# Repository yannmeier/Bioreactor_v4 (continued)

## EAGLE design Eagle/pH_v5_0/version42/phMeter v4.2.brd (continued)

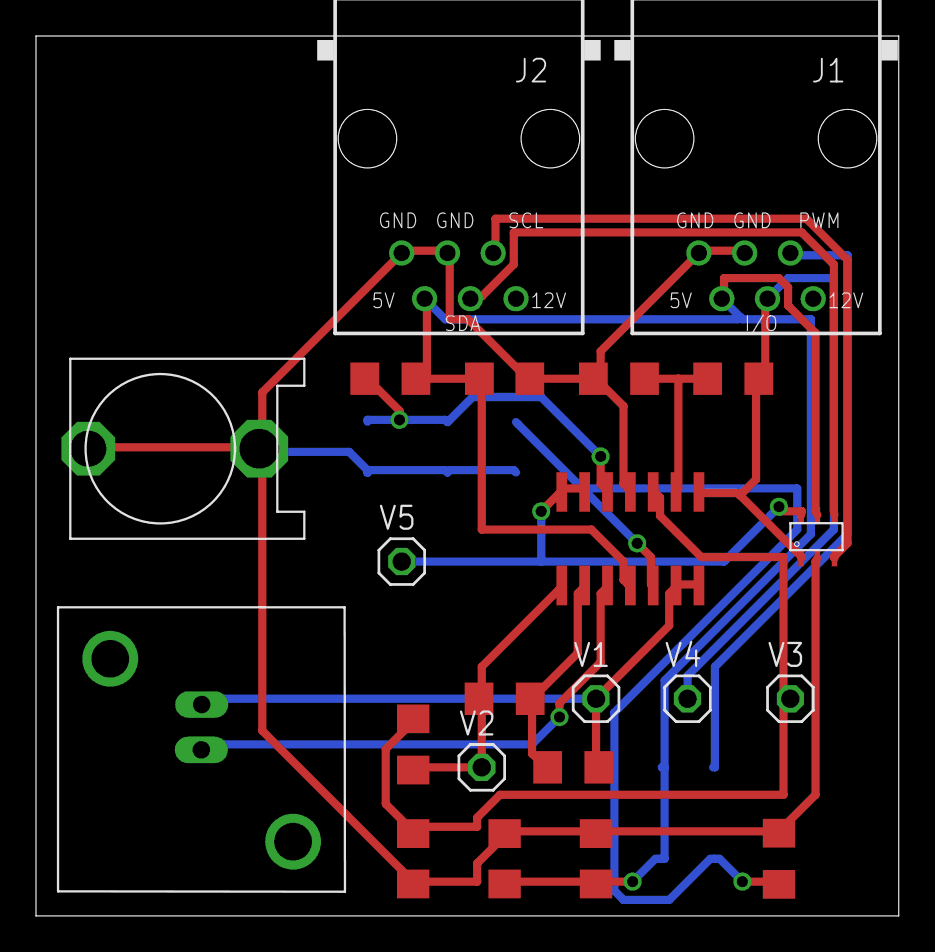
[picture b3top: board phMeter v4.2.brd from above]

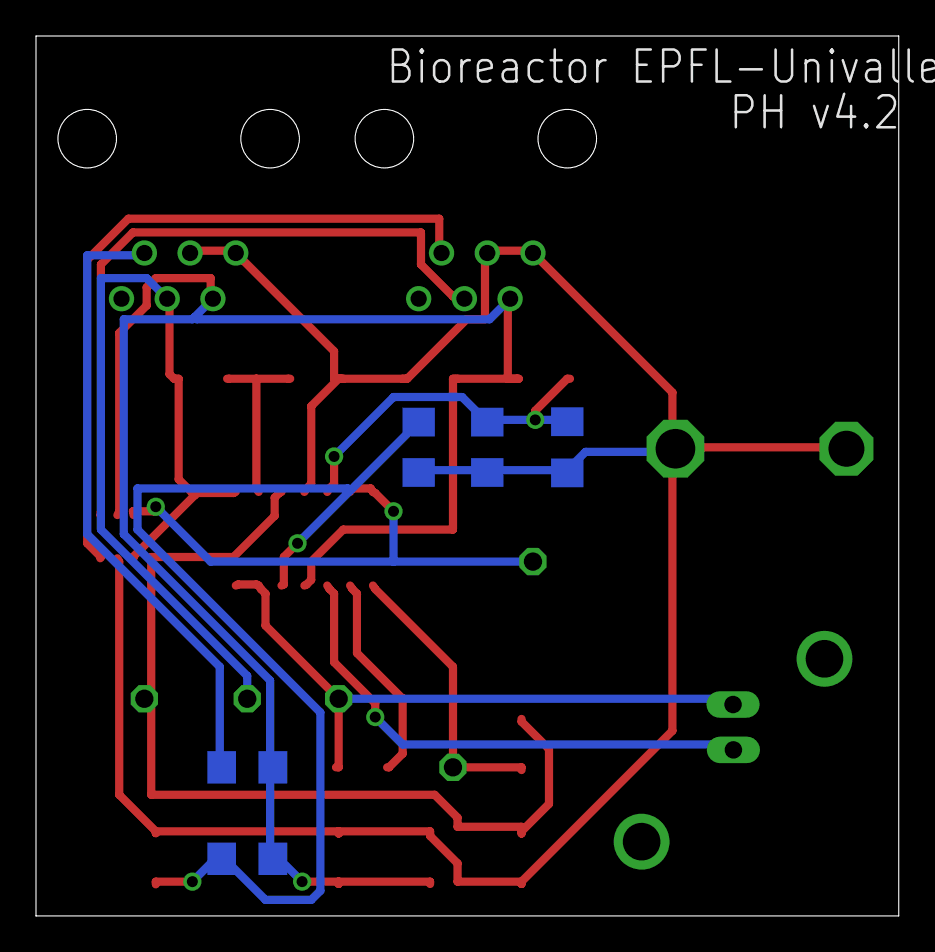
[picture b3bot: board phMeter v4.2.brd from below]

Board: 2 copper layers, 47.9 x 48.9 mm, 27 parts (5 on the bottom side), 15 nets.

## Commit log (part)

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2016-04-12 SPI slave receiving packets, started to implement parsing
2016-04-13 swapped flex connector on LCD SPI, changed D11 pin by the SS/RXLED pin instead, removed SPI pull-up + diode
2016-04-13 send last parameters instead of last logs to the SPI slave LCD
2016-04-13 code cleaning
2016-04-13 Added files via upload
2016-04-13 Created git file in repository
    First Case Prototype
2016-04-13 changed read/write rights n CAD folder
2016-05-07 Fix problem to set parameters with single letter
2016-05-19 bioreactor v4.2 revision, Lora Reset pin on D5, operation at 8MHz, 3.3V. The Flex cable is now exporting 12V instead of 5V (careful, not compatible with LCD V0.2 sudo git add --all), I2C ports are on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
2016-05-24 panelized LCD board v1_0
2016-06-03 corrected bioreactor board for microcircuitos (0.25mm clearance)
2016-07-20 modifications Eric
2016-07-27 CAD files sorted into version folders
2016-07-28 Started working on SPI communication, LCD to master.
2016-08-02 first working SPI communication: transfers one setting at a time. Working on a menu system for the LCD and setting parameters.
2016-08-12 last commit for Eric and Emilien, summer 2016
2016-08-12 Added Documentation and CAD files.
2016-08-16 unziped libraries
2016-10-10 added ref to arduino ide realeases
2016-10-10 debugged version, need to correct onewire to support ds1820, to test the logger(bug here) and lora threads (not compiling)
2016-10-11 error found on eagle brd, LDO 3V3 was disconnected !, need to regenerate the gerbers !
2016-10-11 regenerated gebers
2016-10-11 added more missing breaks in serial switch
2016-10-21 quick clean
2016-10-21 new v4.3, removed bistable control of the stepper, now on pins A0/A1/D8/D9, control sequence must be adapted in the arduino code. Started to work on the ph_V5.0 board, need to add two steppers and th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
2016-10-31 started design of the phv5.0 board, conductommetry is still missing, stepper to be rerouted to use one single port would be better !
2016-11-01 finished phv5.0 board, need to dimension correctly the pH resistors and conductometry resistors and capa (not dimensionned yet !! careful not to solder anything)
2016-11-09 reviewed LCD board with fle cable for button
2016-11-15 double carriage return for set epoch
2016-12-06 modif on md file
2016-12-06 adapted parameters table
2016-12-06 Rename V4_PARAMS20161206 - Sheet1.csv to V4_PARAMS20161206.csv
2016-12-08 corected BCN connector side on phv5
2016-12-08 minor change to the state machines table
2016-12-09 added multiple ports support on SST library
2016-12-12 Added SMA LoRa antenna for 4.3 ref #18, same needs to be done for the pH board
2016-12-12 Added SMA LoRa antenna for phV5 board extra mistakes fixed with DRC close #18
2016-12-13 exchanged pins D6 and D12 for PID on PWM closes #13
2016-12-13 Added Comment not to solder I2C pull-ups closes #22
2016-12-14 Added Support Old Flash versions closes #17 Weight Thread tested, PID optimized
2016-12-14 testing new stepper code
2016-12-15 small changes to readme
2016-12-15 extra features to solve weight bugs
2016-12-17 improved weight error management
2016-12-17 implemented nilSemaphores and changed priority order
2016-12-17 Cleanup libraries
2016-12-17 Put back tests !
2016-12-17 Update Onewire ... without testing
2016-12-17 Update HX711 ... without testing
2016-12-17 Start description to change IDE
2016-12-17 Work in preogress to allow to use other IDE
2016-12-17 Change files to make the project compatible with eclipse
2016-12-18 Create test
2016-12-18 Add images
2016-12-19 edited gitignore rules
2016-12-19 removed protection causing problem and extra include balise
2016-12-19 removed bug inducing include
2016-12-19 changed conflicting declaration of TRUE
2016-12-19 Added PID safety measure on sedimentation and emptying closes #29
2016-12-19 prevent log explosion on weight error
2016-12-19 4mm holes on mainboard
2016-12-19 improved PID safety implementation
2016-12-21 Added jack connector for PID closes #40
2016-12-21 Changed pin Mapping to allow PWM food control Need to Adapat Arduino code !!!
2016-12-21 Changed DS18B20 package to MSOP8
2016-12-21 regenerated gerbers for 4.4, displaying values
2016-12-21 Heater contacts PCB closes #35 Check dimensions are ok
2016-12-23 Changing LCD SPI communication protocol Modified files rights
2016-12-23 implementing new LCD protocol
2016-12-23 SPI comm corrections and cleaning
2016-12-23 cleaning LCD code
2016-12-23 minor corrections, need to revise LCD functions set
2016-12-23 now compiling
2017-01-06 work in progress
2017-01-06 CAD v4.3 Freecad test
2017-01-06 fix front&back sides
2017-01-06 Fix bugs on front side plate
2017-01-08 Add bash script to generate BOM.tsv
2017-01-08 Update BOM script
2017-01-08 fix spelling
2017-01-09 Start LCD
2017-01-09 FreeCAD update with DXF files for direct laser cutting
2017-01-09 CAD update
2017-01-09 update of DXF CAD
2017-01-09 update DXF 4mm
2017-01-09 fixing dimensions
2017-01-09 CAD fixing peristatic pump screw angle
2017-01-09 fixing SVG
2017-01-10 resolve error CAD
2017-01-10 big loading cell dimensions add
2017-01-10 Holes size reduced to 3.2mm fix #50 ref #39
2017-01-11 CAD hole stepper fix
2017-01-11 Install details for OSX
2017-01-11 removed extra Lib folder
2017-01-12 3D print for magnet holder test2
2017-01-12 CAD pcb holes entry fix
2017-01-12 New Time library issue
    Time should be directly downloaded from Arduino software and include TimeLib.h
2017-01-12 updated DXF files
2017-01-13 CAD for Alu tank foundation
2017-01-13 temperature sensor hole added
2017-01-13 fix alu foundation
2017-01-13 pcb master holes fix
2017-01-16 hole size changed to 3.2mm diameter closes #39
2017-01-16 fix on CAD magnet holder
2017-01-16 Progress on pH board v6_0 with DRV8811
2017-01-22 Remove the setAndSave and just put set
2017-01-22 Update cad to have big hole behind
2017-01-23 Update PID to signed value
    This allows to put back the setAndSaveParameter
2017-01-23 adding separate button and main boards gerbers for LCD 1.1
2017-01-23 All connectors on the connector slot
2017-01-23 All connectors BUT the PID on external slot, DRV8811 to be routed closes #57 ref #47
2017-01-25 Default calibration with gr precision ref #42 To be redone once BJT is connected Dynamic calibration: to be implmented
2017-01-25 fix socket entry closes #67
2017-01-27 Add test stepper
2017-01-27 progress on phv6, mem select now on A3, LoRa reset on A1, Stepper 1(PWM D9, dir D8), Stepper 2(PWM D10, dir D5)
2017-01-27 shortened boards by 1mm, closes #68
2017-01-27 silk screen correction, need to optimize the current limiting resistors on 4.5
2017-01-29 Small alu foundation
2017-01-30 correction on PID labelling, closes #71
2017-02-03 update gitignore
2017-02-03 Update time
2017-02-03 correct stepper
2017-02-04 Change PID
2017-02-04 Update docs
2017-02-04 Improve gitignore
2017-02-04 In progress
2017-02-04 Fix bug in PARAM_STATUS
2017-02-05 correted PID diode, 4.5 finished, closes #72, ref #47
2017-02-05 corrected powerFET labelling
2017-02-05 Update heating.md
    minor correction
2017-02-05 Update HX711 library
2017-02-05 Work in progress
    - get weight in a reliable way. We need 4 consecutive values that are less than 10% different
    - ability to calibrate the weight (check the menu 'w') and to test
    - add flag PARAM_ERROR to have all the error flags in one variable
2017-02-05 Allow to test the weight from the menu "m"
2017-02-05 add enable and disable
2017-02-06 update comments
2017-02-07 Update HX711
2017-02-07 Invert weight and fix bugs
2017-02-07 Remove debug lines
2017-02-07 Set theme jekyll-theme-tactile
2017-02-08 work in progres
2017-02-08 documentation in progress
2017-02-08 Set theme jekyll-theme-midnight
2017-02-08 Update weight callibration
2017-02-09 Add error code in parameters
2017-02-09 Simplify test of weight
2017-02-09 Add loading cell description
2017-02-09 add link to loading cell
2017-02-09 Add more information in the s(t)atus command
2017-02-09 Allow to disable food control
2017-02-09 Add uptime in epoch
2017-02-09 add hx711 in the code
2017-02-09 add faq
2017-02-09 Add debug in HX711 library
2017-02-09 Add a faq about current state
2017-02-15 added high side power switch with 5.6V zener on V4.5, drafted hack modif on 4.4, To be tested
2017-02-15 pretty sch for 4.5
2017-02-22 Disable heating during sedimentation and pump out
2017-02-22 improve doc
2017-02-22 Add memory to stepper
2017-03-01 Add poster STIL 2017
2017-03-04 Work in progress renamed parameters
2017-03-05 JTAG on top
2017-03-25 upade memory test
2017-03-27 update parameter
2017-04-01 change resistor select flash to 1k
2017-04-01 Add tests
2017-04-01 Fix bug in one wire and update librarie
2017-04-02 Improve LOGGER thread enabling
2017-04-02 Add submenu for legger
2017-04-02 Fix bug
2017-04-12 Corrected minor mistakes on pull uo/down lines closes #90 , Gebers to be recreated
2017-04-12 LoRa Antenna moved inward, rerouted more simply the SST Flash memory closes #85 closes #86 closes #87, need to regen Gerbers
2017-04-12 Fix bug with not one wire
2017-04-17 Added LEDs for DRV8811 Stepper Driver closes #83
2017-04-17 changed the SMA edge connector forrpting fot LoRa antenna. Foortptint to be checked, Gerbers to be Regenerated !
2017-04-19 added gerbers
2017-04-26 Add stepper test
2017-05-05 First push SST Migration
2017-05-07 update labels
2017-05-10 Minor changes
2017-05-10 Minor changes and corrections
2017-05-13 Changes to the SST library as well as the example -> Pin was read-only. Issue has been fixed. -> readStatus and readConfig are correct, as well as readFlashID. SST is seemingly correctly initialized.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
2017-05-14 Update serial to have a more general submenu
2017-05-15 Minor changes, debugging in process Issue with the waitUntilDone corrected.
2017-05-15 added block protection register command functions for sst26vf family
2017-05-15 created private flashWREN for the sake of clarity
2017-05-16 Final modifications to class SST.
    Class is now functionnal.
    Tests have been run. One final function is yet to be verified. On testMemory file, last test could not be performmed, so function flashWriteBPR has to be verified.
    Writing, reading and erasing on the library have all been tested and are fully functionnal.
2017-05-17 optimized delays according to SST26 datasheet
2017-06-05 First update on How to build a bioreactor. Minor syntaxic changes in Index and Bill of material.
    Work in progress.
2017-06-05 Addition of How to build thebioreactor. WIP
2017-06-06 Updated images in Assembling document
2017-06-07 Minor changes (mostly aesthetic) in testmemory programm. Final tests for memory have now been run on both SST25 and SST26. Library is fully functionnal on both memory chips.
2017-08-01 Update to stepper test file for V4.5. Test now contains several methods. This is for further implementation into BioMain (Work in progress)
2017-08-01 Changes on stepper Thread ------------------------- -> Stepper thread updated for V4.5 and further -> In definitions in main, added a define Before_45. To be uncommented for boards of V4.4 or before.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
2017-08-08 First changes to LCD programm. Added cursorBlink function in order to see which menu is selected. Work in progress
2017-08-28 Major changes in LCD display and minor change in testStepper
    -> Menu display changed
    ->Blink function updated
    WEIGHT CALIBRATION MUST BE IMPLEMENTED AND SPI COMMUNICATION VERIFIED
2017-08-30 syntax
2017-08-30 change logger interval to 10
2017-08-30 Minor fixes
    Syntaxic errors, Multilog reset to 64
2017-09-01 update code to use less memory
2017-09-01 correct logger failure
2017-09-04 add test cases for memory
2017-09-04 update code to use changed sst library
2017-09-05 Update BOM for new stepper architecture
2017-09-06 improve momry test
2017-09-06 simplify the code and remove ph and gas
2017-09-06 more simplification
2017-09-07 Modification of Stepper test. Frequency set with pwm
